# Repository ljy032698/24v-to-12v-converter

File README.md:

# 24V to 12V Converter

24V에서 12V로 변환해주는 컨버터 회로도 및 PCB입니다.

## 스크린샷

## 사용된 프로그램
- [Kicad](https://kicad.org)

## 라이선스
- [MIT](/LICENSE)

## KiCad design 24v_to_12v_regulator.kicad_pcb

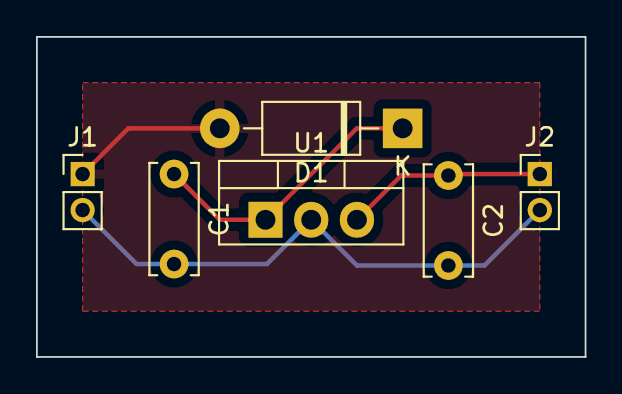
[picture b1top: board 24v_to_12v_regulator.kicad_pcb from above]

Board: 2 copper layers, 30.5 x 17.8 mm, 6 parts (0 on the bottom side), 4 nets.

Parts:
C1, C2: C; C_Disc_D6.0mm_W2.5mm_P5.00mm
D1: 1N4002; D_DO-41_SOD81_P10.16mm_Horizontal
J1, J2: Conn_01x02_Male; PinHeader_1x02_P2.00mm_Vertical
U1: LM7812_TO220; TO-220-3_Vertical

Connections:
+24V: D1.2 (A), J1.1
GND: C1.2, C2.2, J1.2, J2.2, U1.2 (GND)
unnamed: C1.1, D1.1 (K), U1.1 (VI)
unnamed: C2.1, J2.1, U1.3 (VO)

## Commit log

2022-06-07 Initial license
2022-06-07 Initial README.md
2022-06-07 Add kicad.org
2022-06-07 Add screenshots
